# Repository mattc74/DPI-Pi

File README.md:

# DPI-Pi
18Bit DPI &amp; Back Light Driver for Raspi

This is a Small PCB Design aiming at using a parallel RGB 3.5" screen directly from the ras-pi GPIO Pins

The Screen used is: Model No. LQ035NC111 320x240 3.5" and is popular in GameBoy Projects.

Ammendments will need to be made to /boot/config.txt on the pi.

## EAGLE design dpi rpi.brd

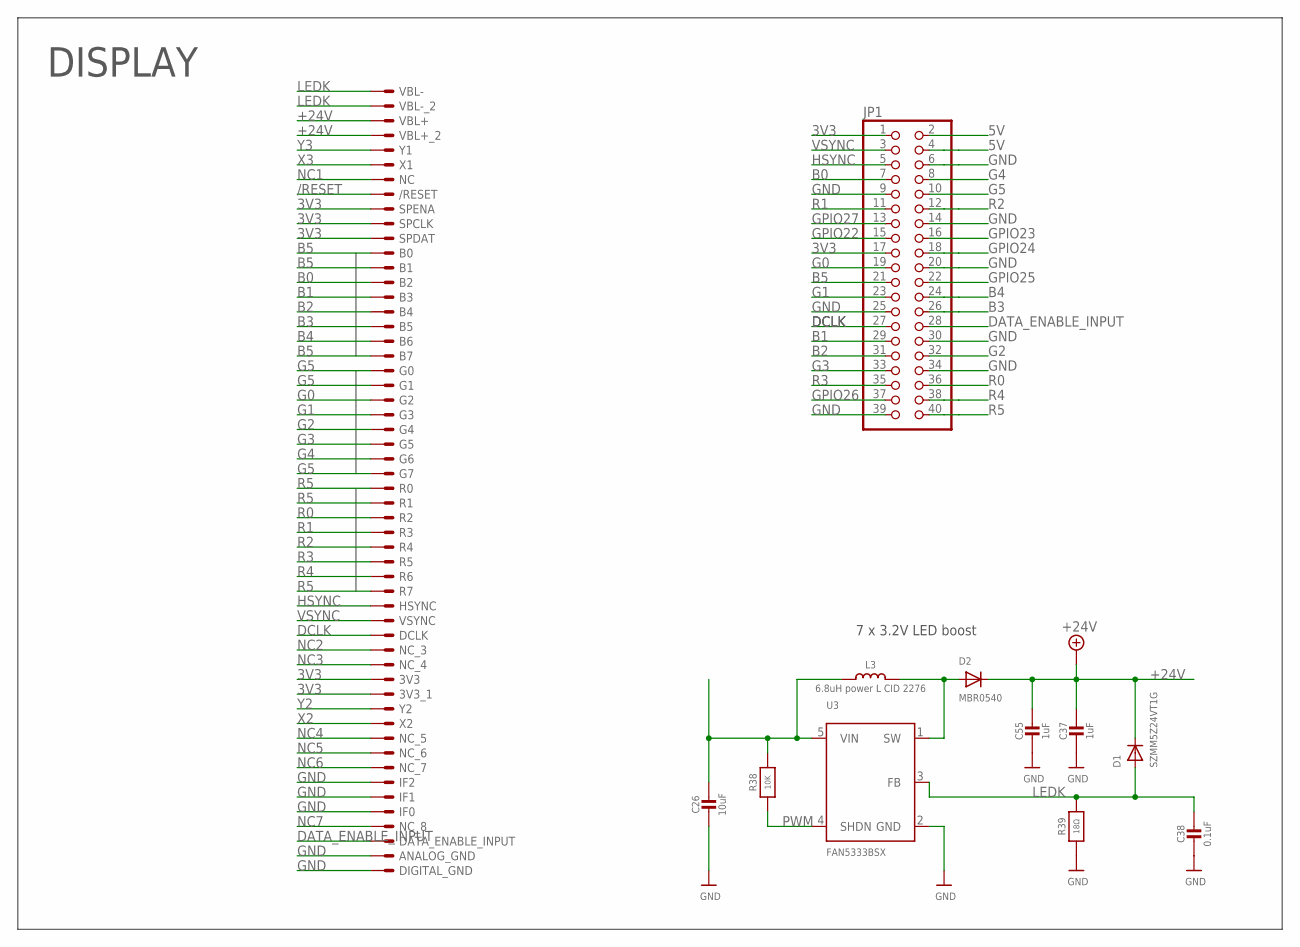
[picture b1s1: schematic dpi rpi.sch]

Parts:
C26: 10uF; _0805MP
C37, C55: 1uF; _0805MP
C38: 0.1uF; _0805MP
D1: SZMM5Z24VT1G; SMADIODE
D2: MBR0540; SOD-123
JP1: PINHD-2X20; 2X20
L3: 6.8uH power L CID 2276; INDUCTOR_5X5MM_NR5040_NOTHERMALS
R38: 10K; _0805MP
R39: 18Ω; _0805MP
U3: FAN5333BSX; SOT23-5@1
U$5: 51296-5494; 51296

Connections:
3V3: C26.1, JP1.1, JP1.17, L3.P$1 (1), R38.2, U3.5 (VIN), U$5.9 (SPENA), U$5.10 (SPCLK), U$5.11 (SPDAT), U$5.41 (3V3), U$5.42 (3V3_1)
5V: JP1.2, JP1.4
+24V: C37.1, C55.1, D1.C, D2.C, U$5.3 (VBL+), U$5.4 (VBL+_2)
/RESET: U$5.8 (/RESET)
B0: JP1.7, U$5.14 (B2)
B1: JP1.29, U$5.15 (B3)
B2: JP1.31, U$5.16 (B4)
B3: JP1.26, U$5.17 (B5)
B4: JP1.24, U$5.18 (B6)
B5: JP1.21, U$5.12 (B0), U$5.13 (B1), U$5.19 (B7)
DATA_ENABLE_INPUT: JP1.28, U$5.52 (DATA_ENABLE_INPUT)
DCLK: JP1.27, U$5.38 (DCLK)
G0: JP1.19, U$5.22 (G2)
G1: JP1.23, U$5.23 (G3)
G2: JP1.32, U$5.24 (G4)
G3: JP1.33, U$5.25 (G5)
G4: JP1.8, U$5.26 (G6)
G5: JP1.10, U$5.20 (G0), U$5.21 (G1), U$5.27 (G7)
GND: C26.2, C37.2, C38.2, C55.2, JP1.6, JP1.9, JP1.14, JP1.20, JP1.25, JP1.30, JP1.34, JP1.39, R39.1, U3.2 (GND), U$5.48 (IF2), U$5.49 (IF1), U$5.50 (IF0), U$5.53 (ANALOG_GND), U$5.54 (DIGITAL_GND)
GPIO22: JP1.15
GPIO23: JP1.16
GPIO24: JP1.18
GPIO25: JP1.22
GPIO26: JP1.37
GPIO27: JP1.13
HSYNC: JP1.5, U$5.36 (HSYNC)
LEDK: C38.1, D1.A, R39.2, U3.3 (FB), U$5.1 (VBL-), U$5.2 (VBL-_2)
unnamed: D2.A, L3.P$2 (2), U3.1 (SW)
NC1: U$5.7 (NC)
NC2: U$5.39 (NC_3)
NC3: U$5.40 (NC_4)
NC4: U$5.45 (NC_5)
NC5: U$5.46 (NC_6)
NC6: U$5.47 (NC_7)
NC7: U$5.51 (NC_8)
PWM: R38.1, U3.4 (SHDN)
R0: JP1.36, U$5.30 (R2)
R1: JP1.11, U$5.31 (R3)
R2: JP1.12, U$5.32 (R4)
R3: JP1.35, U$5.33 (R5)
R4: JP1.38, U$5.34 (R6)
R5: JP1.40, U$5.28 (R0), U$5.29 (R1), U$5.35 (R7)
VSYNC: JP1.3, U$5.37 (VSYNC)
X2: U$5.44 (X2)
X3: U$5.6 (X1)
Y2: U$5.43 (Y2)
Y3: U$5.5 (Y1)

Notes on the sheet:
DISPLAY
7 x 3.2V LED boost

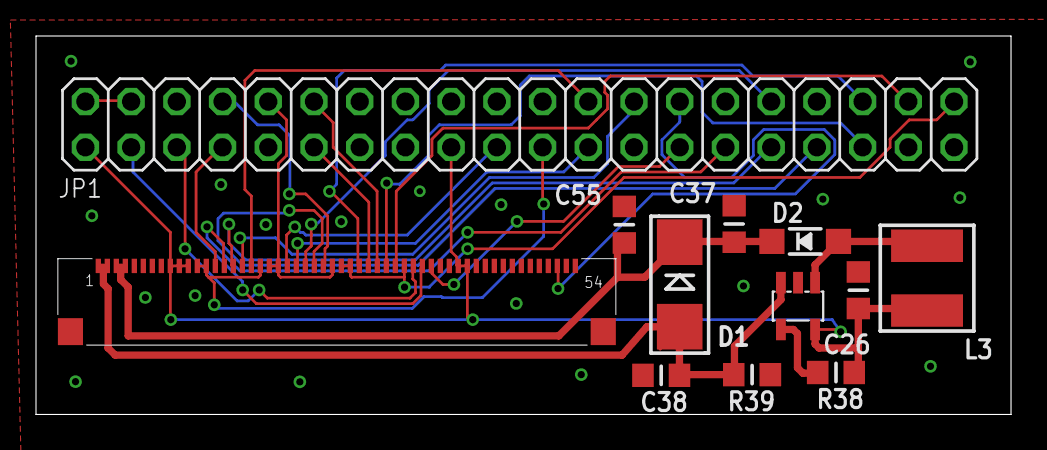
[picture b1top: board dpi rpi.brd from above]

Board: 2 copper layers, 54.2 x 21.0 mm, 12 parts (0 on the bottom side), 29 nets.

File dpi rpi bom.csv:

Qty,Value,Device,Package,Parts,Description
1,,PINHD-2X20,2X20,JP1,PIN HEADER
1,0.1uF,CAP_CERAMIC_0805MP,_0805MP,C38,Ceramic Capacitors
1,10K,RESISTOR_0805MP,_0805MP,R38,Resistors
1,10uF,CAP_CERAMIC_0805MP,_0805MP,C26,Ceramic Capacitors
1,18Ω,RESISTOR_0805MP,_0805MP,R39,Resistors
2,1uF,CAP_CERAMIC_0805MP,_0805MP,"C37, C55",Ceramic Capacitors
1,51296-5494,51296-5494,51296,U$5,"Molex   0.5mm Pitch, Bottom contacts, 54 positions"
1,6.8uH power L CID 2276,INDUCTORNR5040,INDUCTOR_5X5MM_NR5040_NOTHERMALS,L3,Inductors
1,FAN5333BSX,FAN5331,SOT23-5@1,U3,FAN5331 - LED/OLED 20V Boost Converter
1,MBR0540,DIODESOD-123,SOD-123,D2,Diode
1,SZMM5Z24VT1G,DIODESMA,SMADIODE,D1,Diode

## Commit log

2017-11-04 Rename confix.txt to config.txt
2017-11-06 Add files via upload
    Updated with Helders tidy up of the crappy auto-routing for RGB lines.
